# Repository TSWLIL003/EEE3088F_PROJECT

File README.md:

**Project Overview**

This repository contains the design files and documentation for the power subsystem of the EEE3088F 2025 Micro-mouse project. The power module is responsible for providing regulated power to all components of the maze-solving robot while adhering to strict budget constraints.

**Key Features**

Dual-voltage power supply (3.3V @ 300mA and 5V @ 1.5A)

Battery charging system with two charging modes (200mA and 600mA)

USB-C power input with 9V output capability

Motor control for 4 DC motors (2x 200mA, 2x 500mA)

I2C-based battery monitoring via INA219

Low-power switch (<30μA in OFF state)

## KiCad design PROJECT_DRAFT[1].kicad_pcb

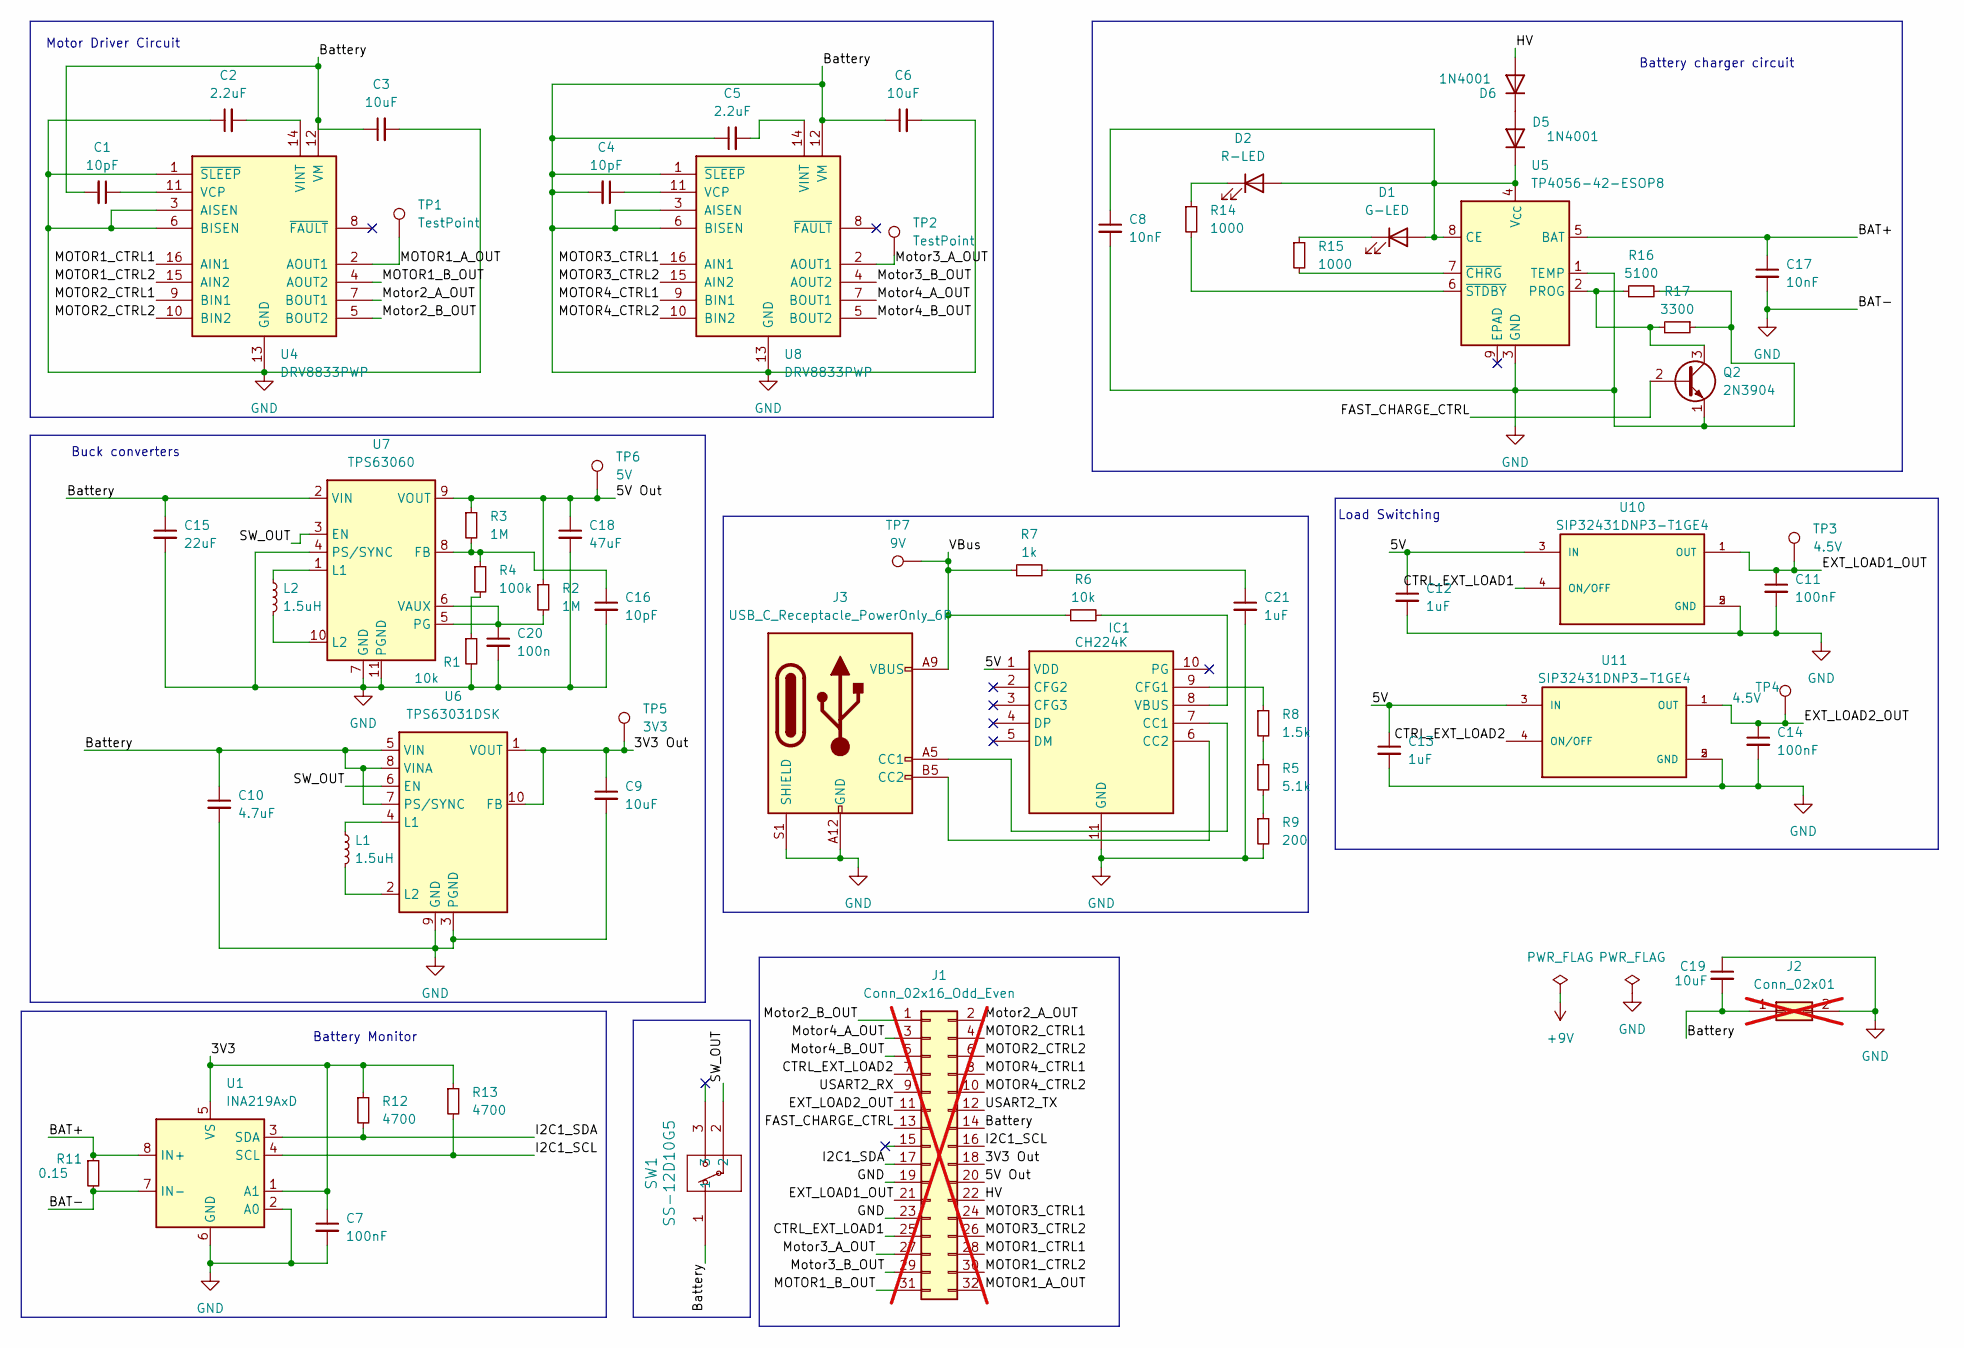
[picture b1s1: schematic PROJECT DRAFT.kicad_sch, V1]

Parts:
C1, C4, C16: 10pF; C_0603_1608Metric_Pad1.08x0.95mm_HandSolder; LCSC C1634
C2: 2.2uF; C_0402_1005Metric_Pad0.74x0.62mm_HandSolder; LCSC C12530
C3, C6, C9: 10uF; CP_EIA-3216-18_Kemet-A_Pad1.58x1.35mm_HandSolder; LCSC C7171
C5: 2.2uF; C_0402_1005Metric_Pad0.74x0.62mm_HandSolder
C7, C11, C14: 100nF; C_0402_1005Metric_Pad0.74x0.62mm_HandSolder; LCSC C1525
C8, C17: 10nF; C_0805_2012Metric_Pad1.18x1.45mm_HandSolder; LCSC C1710
C10: 4.7uF; C_0805_2012Metric_Pad1.18x1.45mm_HandSolder; LCSC C1779
C12, C13: 1uF; C_1206_3216Metric_Pad1.33x1.80mm_HandSolder; LCSC C1848
C15: 22uF; C_1206_3216Metric_Pad1.33x1.80mm_HandSolder; LCSC C12891
C18: 47uF; C_0805_2012Metric_Pad1.18x1.45mm_HandSolder; LCSC C16780
C19: 10uF; CP_EIA-3216-10_Kemet-I_Pad1.58x1.35mm_HandSolder; LCSC C149670
C20: 100n; C_0402_1005Metric_Pad0.74x0.62mm_HandSolder; LCSC C1525
C21: 1uF; C_1206_3216Metric_Pad1.33x1.80mm_HandSolder
D1: G-LED; LED_0603_1608Metric_Pad1.05x0.95mm_HandSolder; LCSC C2286
D2: R-LED; LED_0603_1608Metric_Pad1.05x0.95mm_HandSolder; LCSC C2286
D5, D6: 1N4001; D_DO-41_SOD81_P10.16mm_Horizontal
IC1: CH224K; SOP100P600X180-11N; Manufacturer_Part_Number CH224K; LCSC C970725
J1: Conn_02x16_Odd_Even; PinHeader_2x16_P2.54mm_Vertical; not fitted
J2: Conn_02x01; JST_PH_B2B-PH-K_1x02_P2.00mm_Vertical; not fitted
J3: USB_C_Receptacle_PowerOnly_6P; USB_C_Receptacle_GCT_USB4125-xx-x-0190_6P_TopMnt_Horizontal; LCSC C168701
L1, L2: 1.5uH; L_0402_1005Metric_Pad0.77x0.64mm_HandSolder; LCSC C84470
Q2: 2N3904; SOT-23; LCSC C18536
R1: 10k; R_0805_2012Metric_Pad1.20x1.40mm_HandSolder; LCSC C17414
R2, R3: 1M; R_0805_2012Metric_Pad1.20x1.40mm_HandSolder; LCSC C17514
R4: 100k; R_0805_2012Metric_Pad1.20x1.40mm_HandSolder; LCSC C17900
R5: 5.1k; R_0201_0603Metric_Pad0.64x0.40mm_HandSolder; LCSC C23186
R6: 10k; R_0805_2012Metric_Pad1.20x1.40mm_HandSolder
R7: 1k; R_1206_3216Metric_Pad1.30x1.75mm_HandSolder; LCSC C4410
R8: 1.5k; R_0805_2012Metric_Pad1.20x1.40mm_HandSolder; LCSC C4310
R9: 200; R_0603_1608Metric_Pad0.98x0.95mm_HandSolder; LCSC C8218
R11: 0.15; R_1206_3216Metric_Pad1.30x1.75mm_HandSolder; LCSC C149670
R12, R13: 4700; C_0805_2012Metric_Pad1.18x1.45mm_HandSolder; LCSC C17673
R14, R15: 1000; R_1206_3216Metric_Pad1.30x1.75mm_HandSolder; LCSC C4410
R16: 5100; R_0603_1608Metric_Pad0.98x0.95mm_HandSolder; LCSC C23186
R17: 3300; R_0603_1608Metric_Pad0.98x0.95mm_HandSolder; LCSC C22978
SW1: SS-12D10G5; SS-12D10G5_XKB; LCSC C2884744
TP1, TP2: TestPoint; TestPoint_Pad_2.5x2.5mm
TP3, TP4: 4.5V; TestPoint_Pad_2.5x2.5mm
TP5: 3V3; TestPoint_Pad_2.5x2.5mm
TP6: 5V; TestPoint_Pad_2.5x2.5mm
TP7: 9V; TestPoint_Pad_2.5x2.5mm
U1: INA219AxD; SOIC-8_3.9x4.9mm_P1.27mm; LCSC C87469
U4: DRV8833PWP; TSSOP-16-1EP_4.4x5mm_P0.65mm_EP3x3mm_ThermalVias; LCSC C50506
U5: TP4056-42-ESOP8; SOIC-8-1EP_3.9x4.9mm_P1.27mm_EP2.41x3.3mm_ThermalVias
U6: TPS63031DSK; WSON-10-1EP_2.5x2.5mm_P0.5mm_EP1.2x2mm; LCSC C15516
U7: TPS63060; Texas_S-PWSON-N10; LCSC C48567
U8: DRV8833PWP; TSSOP-16-1EP_4.4x5mm_P0.65mm_EP3x3mm; LCSC C50506
U10, U11: SIP32431DNP3-T1GE4; SON50P120X160X60-5N; PARTREV Rev F; LCSC C727398

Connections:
/3V3: C7.1, R12.1, R13.1, U1.1 (A1), U1.5 (VS)
/3V3 Out: C9.1, J1.18, TP5.1, U6.1 (VOUT), U6.10 (FB)
/5V: C12.1, C13.1, IC1.1 (VDD), U10.3 (IN), U11.3 (IN)
/5V Out: C18.1, J1.20, R2.1, R3.1, TP6.1, U7.9 (VOUT)
/BAT+: C17.1, R11.1, U1.8 (IN+), U5.5 (BAT)
/CTRL_EXT_LOAD1: U10.4 (ON/OFF)
/CTRL_EXT_LOAD1: J1.25
/CTRL_EXT_LOAD2: J1.7, U11.4 (ON/OFF)
/EXT_LOAD1_OUT: C11.1, J1.21, TP3.1, U10.1 (OUT)
/EXT_LOAD2_OUT: C14.1, J1.11, TP4.1, U11.1 (OUT)
/FAST_CHARGE_CTRL: J1.13, Q2.2 (B)
/HV: D6.2 (A), J1.22
/I2C1_SCL: R13.2, U1.4 (SCL)
/I2C1_SCL: J1.16
/I2C1_SDA: R12.2, U1.3 (SDA)
/I2C1_SDA: J1.17
/MOTOR1_A_OUT: J1.32, TP1.1, U4.2 (AOUT1)
/MOTOR1_B_OUT: J1.31, U4.4 (AOUT2)
/MOTOR1_CTRL1: J1.28, U4.16 (AIN1)
/MOTOR1_CTRL2: J1.30, U4.15 (AIN2)
/MOTOR2_CTRL1: J1.4, U4.9 (BIN1)
/MOTOR2_CTRL2: J1.6, U4.10 (BIN2)
/MOTOR3_CTRL1: J1.24, U8.16 (AIN1)
/MOTOR3_CTRL2: J1.26, U8.15 (AIN2)
/MOTOR4_CTRL1: J1.8, U8.9 (BIN1)
/MOTOR4_CTRL2: J1.10, U8.10 (BIN2)
/Motor2_A_OUT: J1.2, U4.7 (BOUT1)
/Motor2_B_OUT: J1.1, U4.5 (BOUT2)
/Motor3_A_OUT: J1.27, TP2.1, U8.2 (AOUT1)
/Motor3_B_OUT: J1.29, U8.4 (AOUT2)
/Motor4_A_OUT: J1.3, U8.7 (BOUT1)
/Motor4_B_OUT: J1.5, U8.5 (BOUT2)
/SW_OUT: SW1.2, U6.6 (EN), U7.3 (EN)
/USART2_RX: J1.9
/USART2_TX: J1.12
/VBus: J3.A9 (VBUS), J3.B9 (VBUS), R6.1, R7.1, TP7.1
GND: C1.2, C2.1, C3.1, C3.2, C4.2, C5.1, C6.1, C6.2, C7.2, C8.2, C9.2, C10.1, C10.2, C11.2, C12.2, C13.2, C14.2, C15.1, C15.2, C16.2, C17.2, C18.2, C19.1, C19.2, C20.2, C21.2, IC1.11 (GND), J1.14, J1.19, J1.23, J2.1, J2.2, J3.A12 (GND), J3.B12 (GND), J3.S1 (SHIELD), Q2.1 (E), R1.2, R9.2, R11.2, R16.2, R17.1, SW1.1, U1.2 (A0), U1.6 (GND), U1.7 (IN-), U4.1 (~SLEEP), U4.3 (AISEN), U4.6 (BISEN), U4.12 (VM), U4.13 (GND), U4.17 (GND), U5.1 (TEMP), U5.3 (GND), U6.3 (PGND), U6.5 (VIN), U6.7 (PS/SYNC), U6.8 (VINA), U6.9 (GND), U6.11 (PGND), U7.2 (VIN), U7.4 (PS/SYNC), U7.7 (GND), U7.11 (PGND), U8.1 (~SLEEP), U8.3 (AISEN), U8.6 (BISEN), U8.12 (VM), U8.13 (GND), U8.17 (GND), U10.2 (GND), U10.5 (GND), U11.2 (GND), U11.5 (GND)
unnamed: C21.1, R7.2
unnamed: C8.1, D1.2 (A), D2.2 (A), D5.1 (K), U5.4 (V_{CC}), U5.8 (CE)
unnamed: D1.1 (K), R15.1
unnamed: D2.1 (K), R14.1
unnamed: D5.2 (A), D6.1 (K)
unnamed: IC1.7 (CC1), J3.A5 (CC1)
unnamed: IC1.6 (CC2), J3.B5 (CC2)
unnamed: IC1.9 (CFG1), R8.1
unnamed: IC1.8 (VBUS), R6.2
unnamed: Q2.3 (C), R16.1, R17.2, U5.2 (PROG)
unnamed: R1.1, R4.2
unnamed: R5.1, R8.2
unnamed: R5.2, R9.1
unnamed: C1.1, U4.11 (VCP)
unnamed: C2.2, U4.14 (VINT)
unnamed: R15.2, U5.7 (~CHRG)
unnamed: R14.2, U5.6 (~STDBY)
unnamed: L1.1, U6.4 (L1)
unnamed: L1.2, U6.2 (L2)
unnamed: C16.1, R3.2, R4.1, U7.8 (FB)
unnamed: L2.1, U7.1 (L1)
unnamed: L2.2, U7.10 (L2)
unnamed: C20.1, R2.2, U7.5 (PG), U7.6 (VAUX)
unnamed: C4.1, U8.11 (VCP)
unnamed: C5.2, U8.14 (VINT)

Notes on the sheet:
Load Switching
Buck converters
Motor Driver Circuit
Battery charger circuit
Battery Monitor

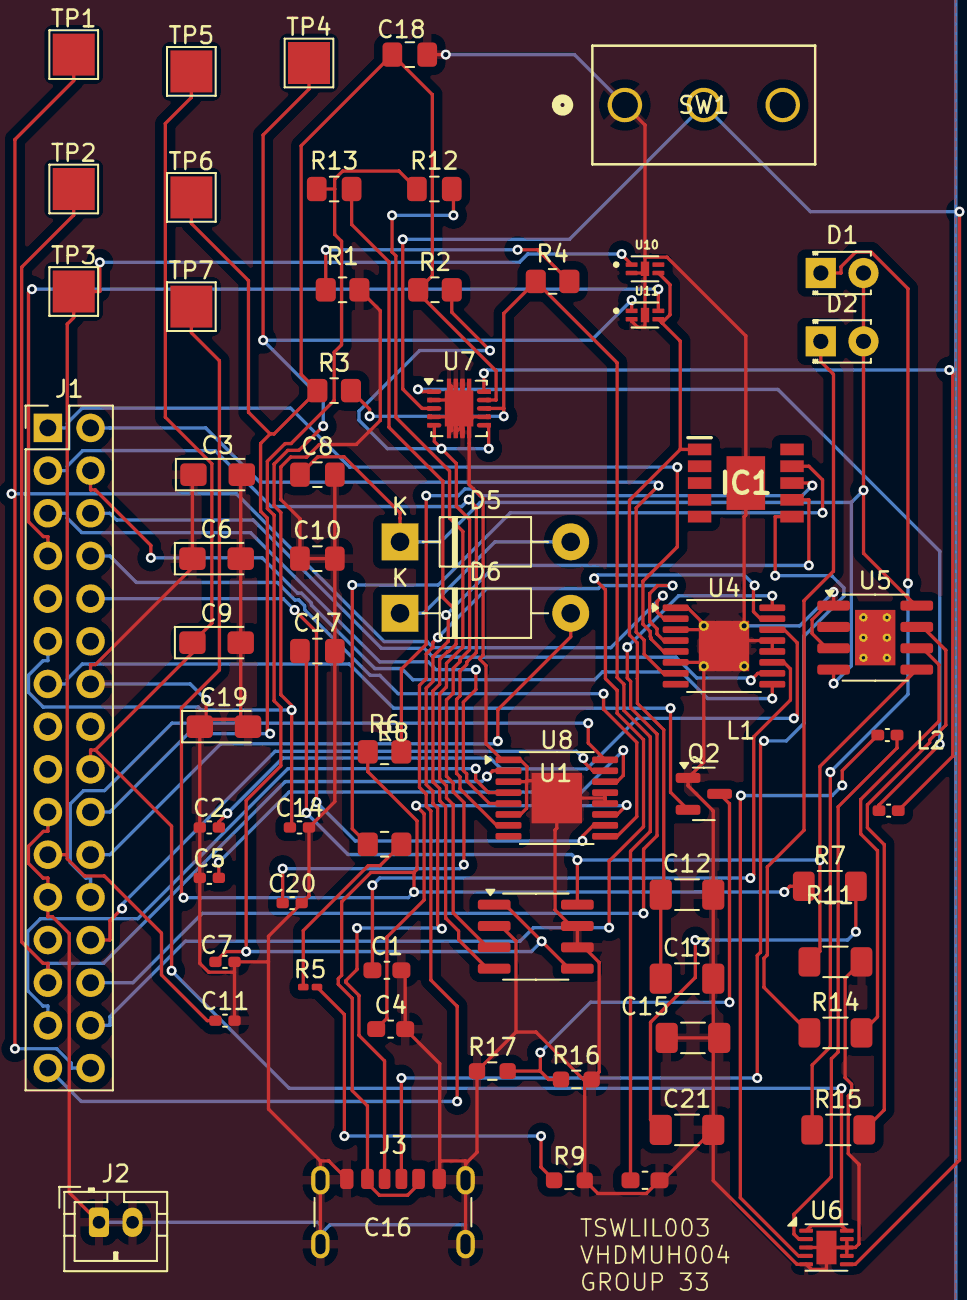
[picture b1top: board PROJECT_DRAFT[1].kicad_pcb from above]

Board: 2 copper layers, 64 parts (0 on the bottom side), 56 nets.

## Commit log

2025-04-24 Update PROJECT DRAFT.kicad_sch
    Added H-bridge circuit for motors
2025-04-24 Update PROJECT_DRAFT[1].kicad_pcb
    Add comments
